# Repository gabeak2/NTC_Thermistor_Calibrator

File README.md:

# NTC_Thermistor_Calibrator
Arduino-based board that can plug 8 NTCs into it, with one of them being a fancy calibrated one.  Then all 8 can be bolted to a piece of metal, and heated with the onboard heater.  The fancy thermistor can be used as a reference, and the other 8 can have their data printed over the USB connection for calibration over the temperature range.

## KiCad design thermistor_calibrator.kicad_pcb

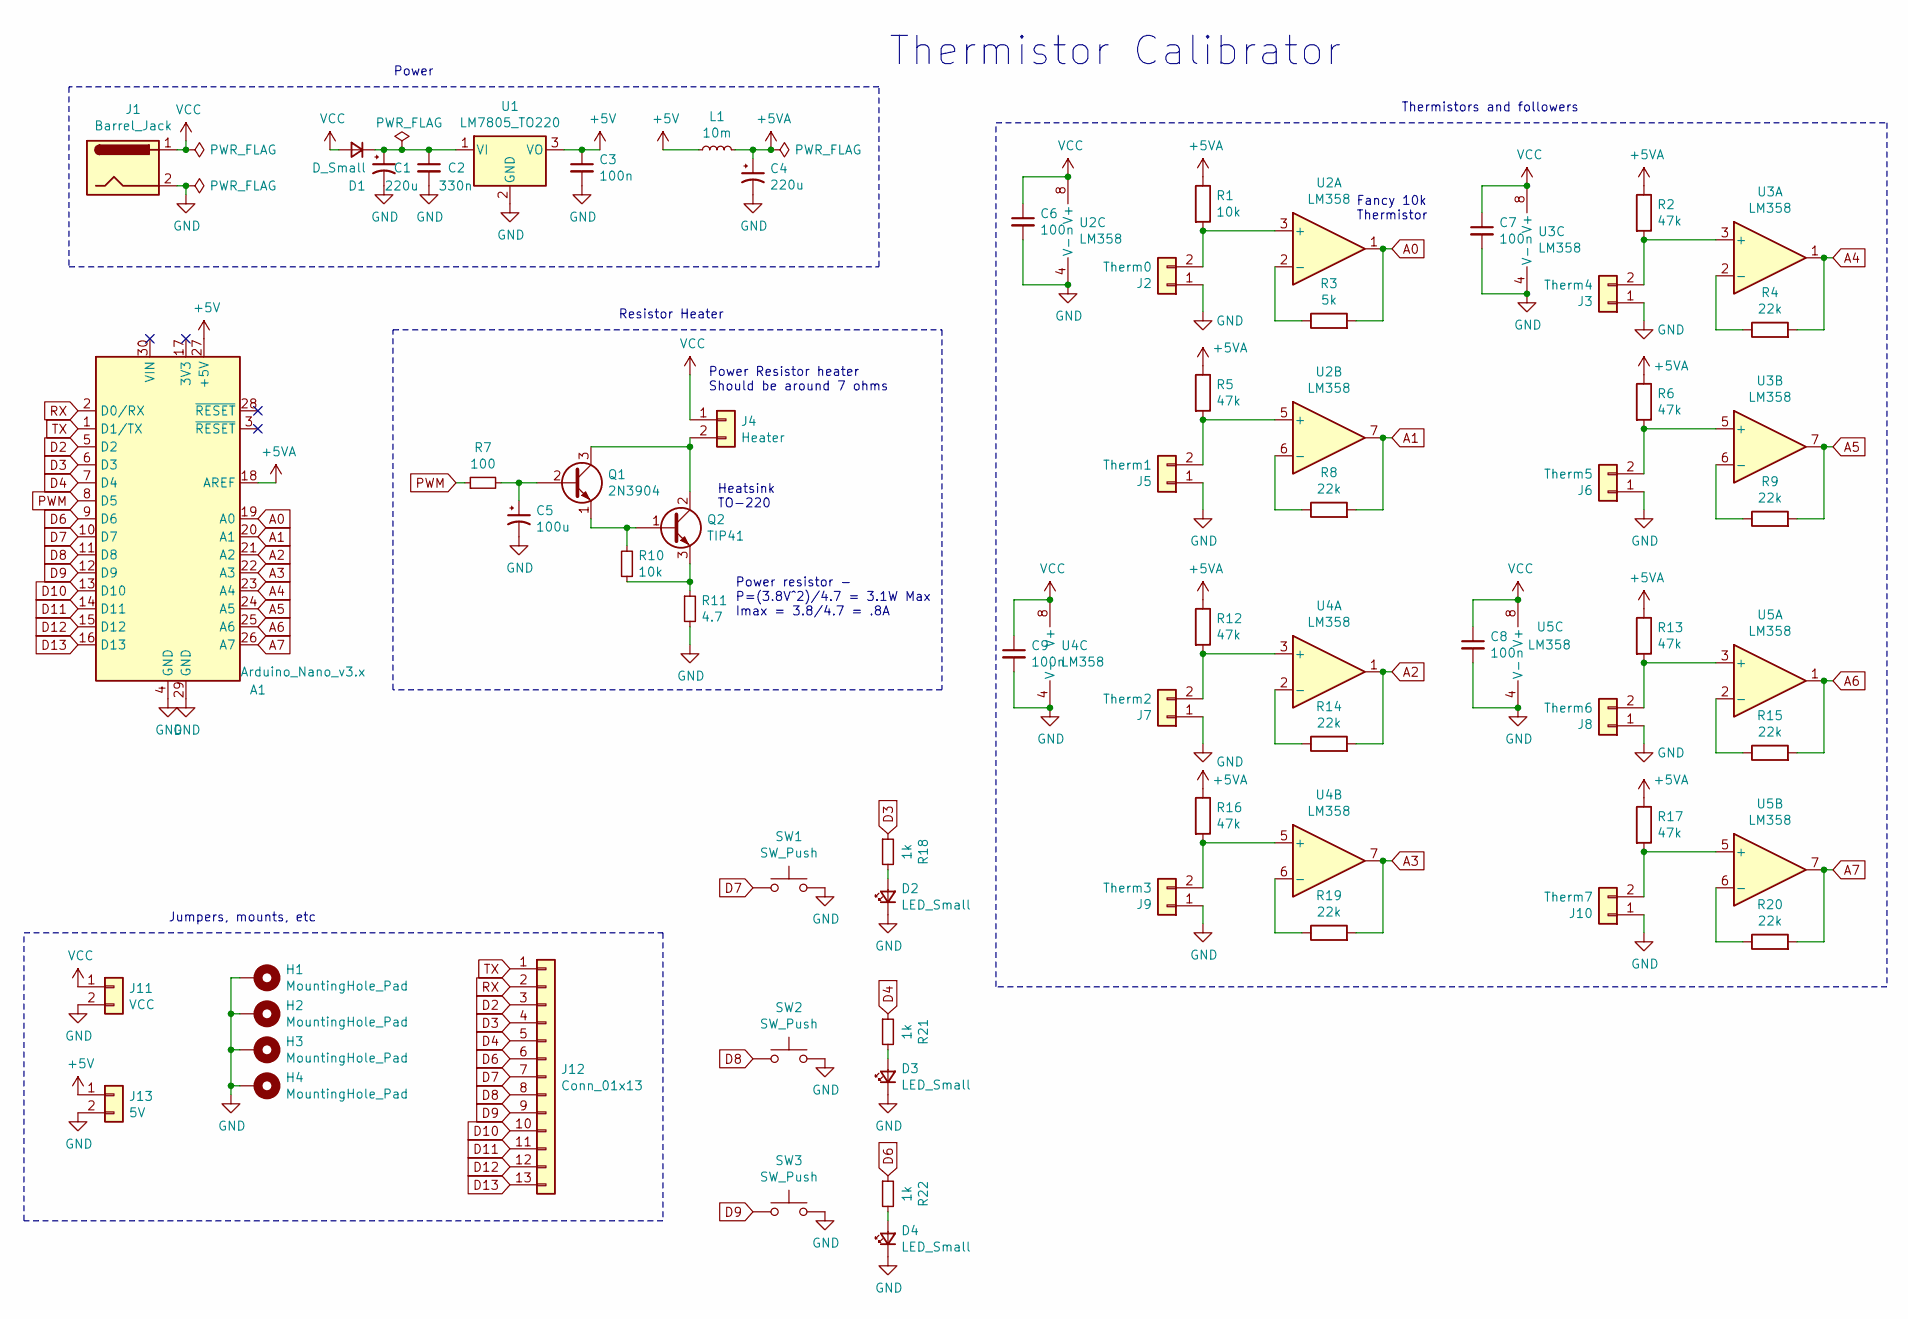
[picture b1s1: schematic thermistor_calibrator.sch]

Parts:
A1: Arduino_Nano_v3.x; Arduino_Nano
C1, C4: 220u; CP_Radial_D8.0mm_P2.50mm
C2: 330n; C_Disc_D3.0mm_W1.6mm_P2.50mm
C3, C6, C7, C8, C9: 100n; C_Disc_D3.0mm_W1.6mm_P2.50mm
C5: 100u; CP_Radial_D8.0mm_P2.50mm
D1: D_Small; D_A-405_P7.62mm_Horizontal
D2, D3, D4: LED_Small; LED_D1.8mm_W3.3mm_H2.4mm
H1, H2, H3, H4: MountingHole_Pad; MountingHole_3.2mm_M3_Pad_Via
J1: Barrel_Jack; Tensility 5.5x2.1mm 54-00166
J2: Therm0; PinSocket_1x02_P2.54mm_Vertical
J3: Therm4; PinSocket_1x02_P2.54mm_Vertical
J4: Heater; PinSocket_1x02_P2.54mm_Vertical
J5: Therm1; PinSocket_1x02_P2.54mm_Vertical
J6: Therm5; PinSocket_1x02_P2.54mm_Vertical
J7: Therm2; PinSocket_1x02_P2.54mm_Vertical
J8: Therm6; PinSocket_1x02_P2.54mm_Vertical
J9: Therm3; PinSocket_1x02_P2.54mm_Vertical
J10: Therm7; PinSocket_1x02_P2.54mm_Vertical
J11: VCC; PinSocket_1x02_P2.54mm_Vertical
J12: Conn_01x13; PinSocket_1x13_P2.54mm_Vertical
J13: 5V; PinSocket_1x02_P2.54mm_Vertical
L1: 10m; L_Toroid_Vertical_L13.0mm_W6.5mm_P5.60mm
Q1: 2N3904; TO-92_Inline
Q2: TIP41; TO-220-3_Vertical
R1, R10: 10k; R_Axial_DIN0204_L3.6mm_D1.6mm_P5.08mm_Horizontal
R2, R5, R6, R12, R13, R16, R17: 47k; R_Axial_DIN0204_L3.6mm_D1.6mm_P5.08mm_Horizontal
R3: 5k; R_Axial_DIN0204_L3.6mm_D1.6mm_P5.08mm_Horizontal
R4, R8, R9, R14, R15, R19, R20: 22k; R_Axial_DIN0204_L3.6mm_D1.6mm_P5.08mm_Horizontal
R7: 100; R_Axial_DIN0204_L3.6mm_D1.6mm_P5.08mm_Horizontal
R11: 4.7; R_Axial_Power_L20.0mm_W6.4mm_P22.40mm
R18, R21, R22: 1k; R_Axial_DIN0204_L3.6mm_D1.6mm_P5.08mm_Horizontal
SW1, SW2, SW3: SW_Push; button_cheapo_ebay_smd
U1: LM7805_TO220; TO-220-3_Vertical
U2, U3, U4, U5: LM358; DIP-8_W7.62mm_Socket

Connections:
+5V: A1.27 (+5V), C3.1, J13.1, L1.1, U1.3 (VO)
+5VA: A1.18 (AREF), C4.1, L1.2, R1.1, R2.1, R5.1, R6.1, R12.1, R13.1, R16.1, R17.1
A0: A1.19 (A0), R3.2, U2.1
A1: A1.20 (A1), R8.2, U2.7
A2: A1.21 (A2), R14.2, U4.1
A3: A1.22 (A3), R19.2, U4.7
A4: A1.23 (A4), R4.2, U3.1
A5: A1.24 (A5), R9.2, U3.7
A6: A1.25 (A6), R15.2, U5.1
A7: A1.26 (A7), R20.2, U5.7
D2: A1.5 (D2), J12.3
D3: A1.6 (D3), J12.4, R18.1
D4: A1.7 (D4), J12.5, R21.1
D6: A1.9 (D6), J12.6, R22.1
D7: A1.10 (D7), J12.7, SW1.1
D8: A1.11 (D8), J12.8, SW2.1
D9: A1.12 (D9), J12.9, SW3.1
D10: A1.13 (D10), J12.10
D11: A1.14 (D11), J12.11
D12: A1.15 (D12), J12.12
D13: A1.16 (D13), J12.13
GND: A1.4 (GND), A1.29 (GND), C1.2, C2.2, C3.2, C4.2, C5.2, C6.2, C7.2, C8.2, C9.2, D2.1 (K), D3.1 (K), D4.1 (K), H1.1, H2.1, H3.1, H4.1, J1.2, J2.1, J3.1, J5.1, J6.1, J7.1, J8.1, J9.1, J10.1, J11.2, J13.2, R11.2, SW1.2, SW2.2, SW3.2, U1.2 (GND), U2.4 (V-), U3.4 (V-), U4.4 (V-), U5.4 (V-)
unnamed: C1.1, C2.1, D1.1 (K), U1.1 (VI)
unnamed: C5.1, Q1.2 (B), R7.2
unnamed: D2.2 (A), R18.2
unnamed: D3.2 (A), R21.2
unnamed: D4.2 (A), R22.2
unnamed: J2.2, R1.2, U2.3 (+)
unnamed: J3.2, R2.2, U3.3 (+)
unnamed: J4.2, Q1.3 (C), Q2.2 (C)
unnamed: J5.2, R5.2, U2.5 (+)
unnamed: J6.2, R6.2, U3.5 (+)
unnamed: J7.2, R12.2, U4.3 (+)
unnamed: J8.2, R13.2, U5.3 (+)
unnamed: J9.2, R16.2, U4.5 (+)
unnamed: J10.2, R17.2, U5.5 (+)
unnamed: Q1.1 (E), Q2.1 (B), R10.2
unnamed: Q2.3 (E), R10.1, R11.1
unnamed: R3.1, U2.2 (-)
unnamed: R4.1, U3.2 (-)
unnamed: R8.1, U2.6 (-)
unnamed: R9.1, U3.6 (-)
unnamed: R14.1, U4.2 (-)
unnamed: R15.1, U5.2 (-)
unnamed: R19.1, U4.6 (-)
unnamed: R20.1, U5.6 (-)
PWM: A1.8 (D5), R7.1
RX: A1.2 (D0/RX), J12.2
TX: A1.1 (D1/TX), J12.1
VCC: C6.1, C7.1, C8.1, C9.1, D1.2 (A), J1.1, J4.1, J11.1, U2.8 (V+), U3.8 (V+), U4.8 (V+), U5.8 (V+)

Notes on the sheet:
Power Resistor heater Should be around 7 ohms
Fancy 10k Thermistor
Power resistor - P=(3.8V^2)/4.7 = 3.1W Max Imax = 3.8/4.7 = .8A
Heatsink TO-220
Resistor Heater
Jumpers, mounts, etc
Power
Thermistor Calibrator
Thermistors and followers

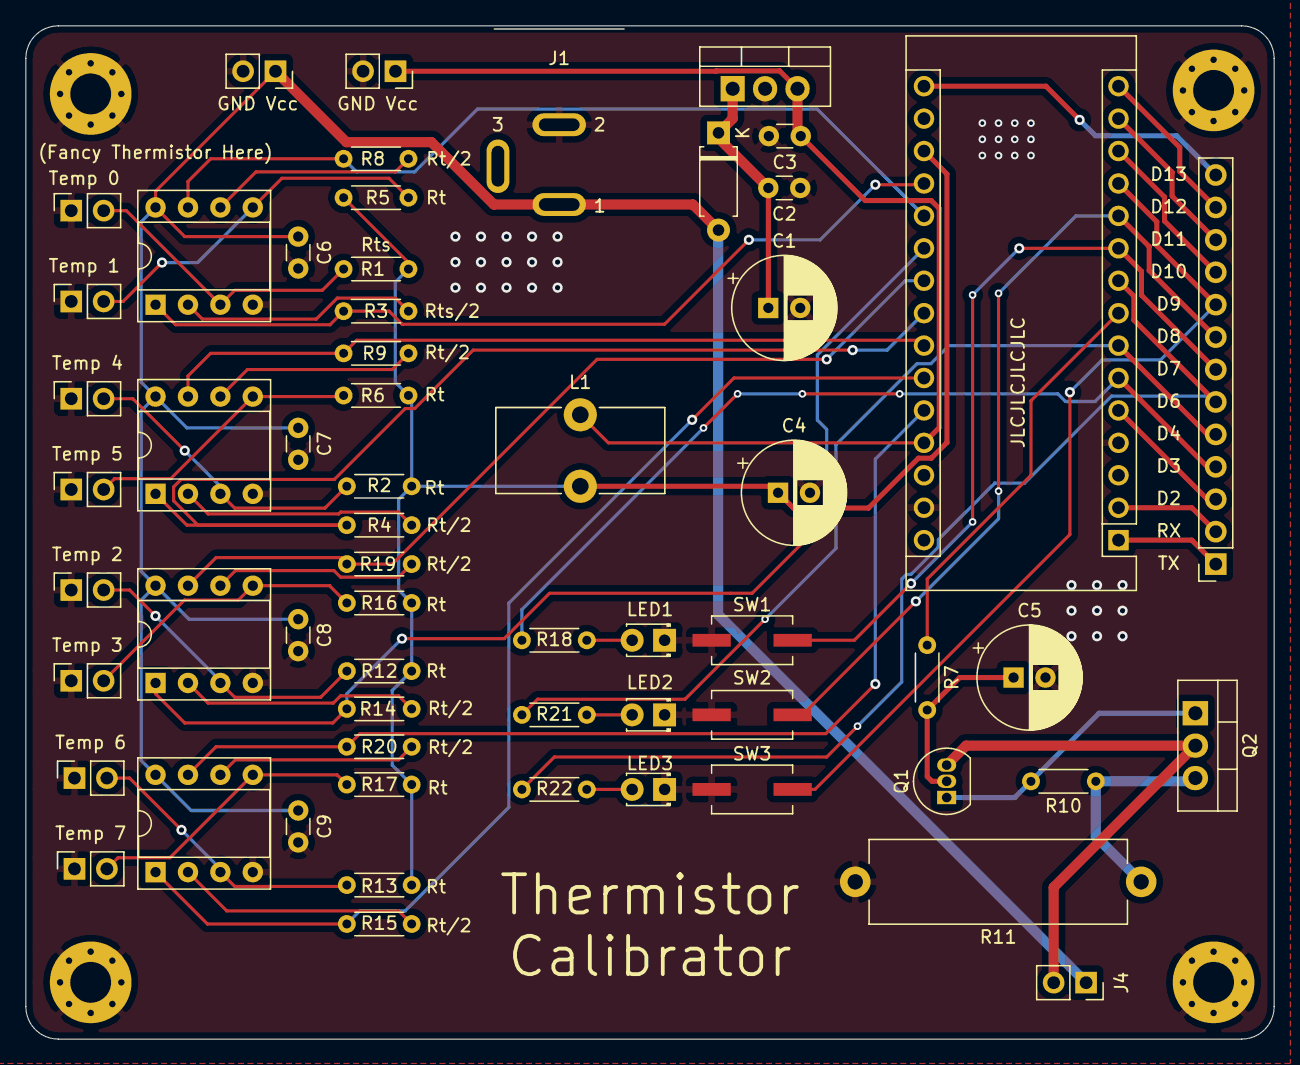
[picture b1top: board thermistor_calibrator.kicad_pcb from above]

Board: 2 copper layers, 97.8 x 79.4 mm, 64 parts (0 on the bottom side), 50 nets.
